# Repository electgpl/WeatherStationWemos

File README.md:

# Estación Meteorológica WiFi v1.0 

Esta es una estación Meteorológica Inalámbrica mediante WiFi, basada en el SoC ESP8266 para la comunicación y los sensores: BMP085/180, DHT11 y LDR.
Para una mejor precisión de medición, la temperatura se extrae del sensor Bosch en lugar del sensor DHT11, quedando así el DHT11 solo para indicar la humedad relativa.
El firmware cuenta con la biblioteca WiFiManager para aumentar la facilidad de autenticación para el usuario y los datos son enviados directamente a ThingSpeak.
Estos datos son enviados cada 5 minutos para mantener las buenas costumbres de frecuencia de datos en el servidor ThingSpeak, en el caso de parámetros meteorológicos no es necesaria la actualización constante de los datos, estos cambian de forma lenta.

## Controles - v1.0

  - Core - **ESP8266 - WEMOS D1 Mini**
  - Sensor de Presión y Temperatura - **BMP085 - BMP180**
  - Sensor de Humedad y Temperatura - **DHT11**
  - Sensor de Luminosidad - **LDR**
  - Botón de configuración para restablecer datos de fabrica
  - Servidor - **ThingSpeak**
  - Control WiFi - **WiFiManager**

## Alimentación

> Diseñado para ser alimentado con fuente de alimentación de 100 a 240Vac 3W

### Diseño

> Diseñado con EAGLE, en solo dos capas con componentes THT para facilitar
> la integración al alumno, el desarrollo del PCB en el hogar y mantener
> el menor costo posible.

### Medición OnLine en Tiempo Real ThingSpeak Channel 128756
https://thingspeak.com/channels/128756

Patrocinado
----
¿Dónde fabricamos nuestros PCBs?
Nuestros PCBs los fabricamos con la empresa PCBWay, esta empresa nos permite realizar pequeñas cantidades como prototipos rápidos para nuestros desarrollos a medida.
También nos permite realizar grandes producciones para realizar proyectos comerciales.
Servicio de prototipo de PCB por tan solo $5 las 10 unidades.
Cada nuevo miembro recibirá un bono de $5, más servicio express de 24Hs o 48Hs.
Servicio de ensamblado de PCB por $88 más envió gratis en todo el mundo, más esténcil, más componentes.
Un servicio de calidad!
https://www.pcbway.es/

License
----

MIT

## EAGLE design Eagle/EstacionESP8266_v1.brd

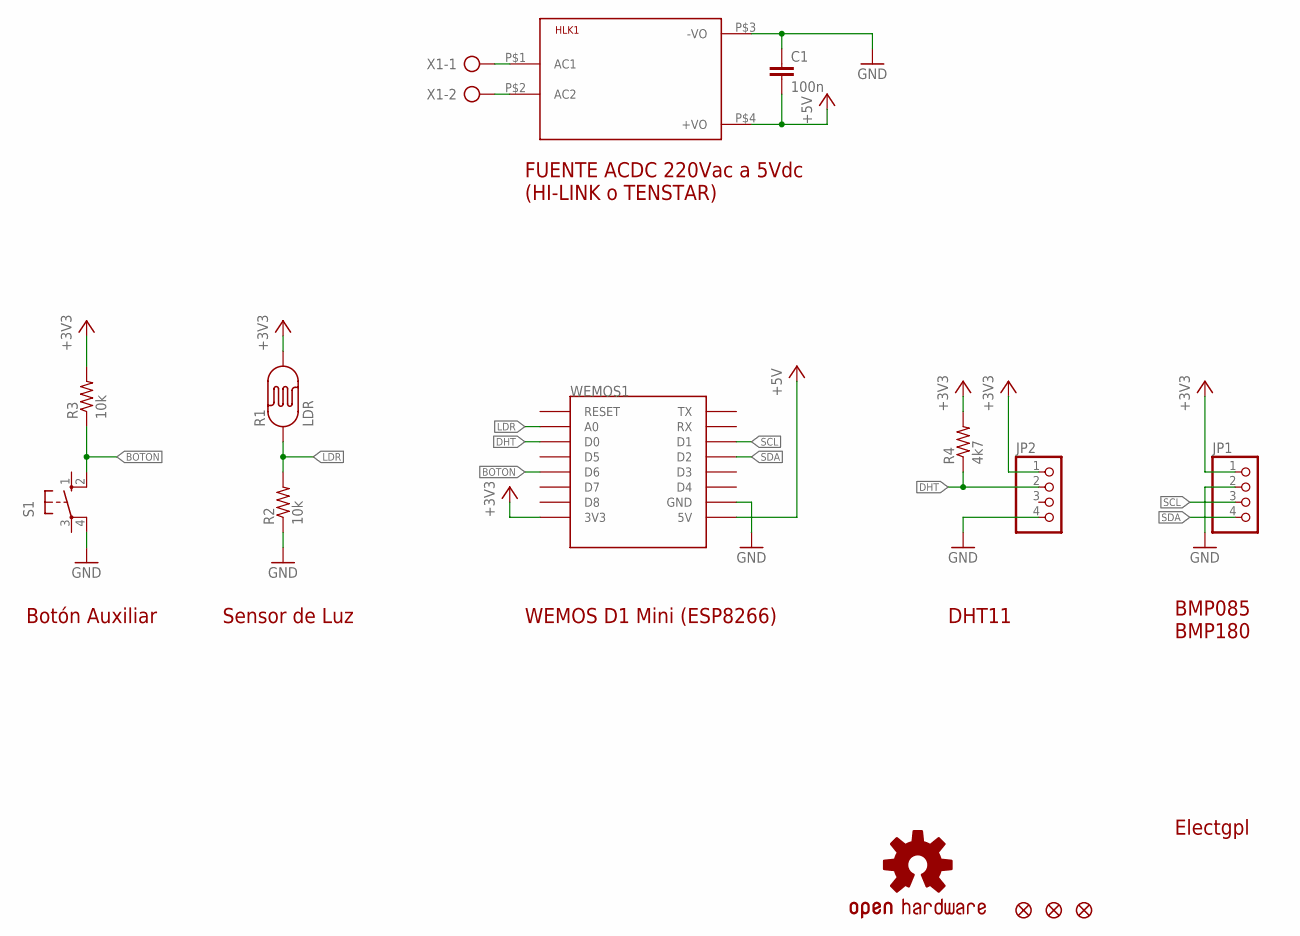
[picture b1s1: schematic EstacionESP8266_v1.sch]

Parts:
C1: 100n; C050-024X044
HLK1: HLK-PM013W; HLK-PM01
JP1, JP2: PINHD-1X4; 1X04
JP3, JP4, JP5: FIDUCIAL1.5X3; FIDUCIAL-1.5X3
R1: LDR; PHOTOCELL
R2, R3: 10k; 0204/7
R4: 4k7; 0204/7
S1: 10-XX; B3F-10XX
U$5: OSHW-LOGOM; OSHW-LOGO-M
WEMOS1: WEMOS-D1-MINI
X1: AK500/2

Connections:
+3V3: JP1.1, JP2.1, R1.2, R3.2, R4.2, WEMOS1.3V3
+5V: C1.2, HLK1.P$4 (+VO), WEMOS1.5V
BOTON: R3.1, S1.2 (S1), WEMOS1.D6
DHT: JP2.2, R4.1, WEMOS1.D0
GND: C1.1, HLK1.P$3 (-VO), JP1.2, JP2.4, R2.1, S1.4 (P1), WEMOS1.GND
LDR: R1.1, R2.2, WEMOS1.A0
unnamed: HLK1.P$1 (AC1), X1.1
unnamed: HLK1.P$2 (AC2), X1.2
SCL: JP1.3, WEMOS1.D1
SDA: JP1.4, WEMOS1.D2

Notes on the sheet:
Electgpl
BMP085 BMP180
DHT11
WEMOS D1 Mini (ESP8266)
Sensor de Luz
Botón Auxiliar
FUENTE ACDC 220Vac a 5Vdc (HI-LINK o TENSTAR)

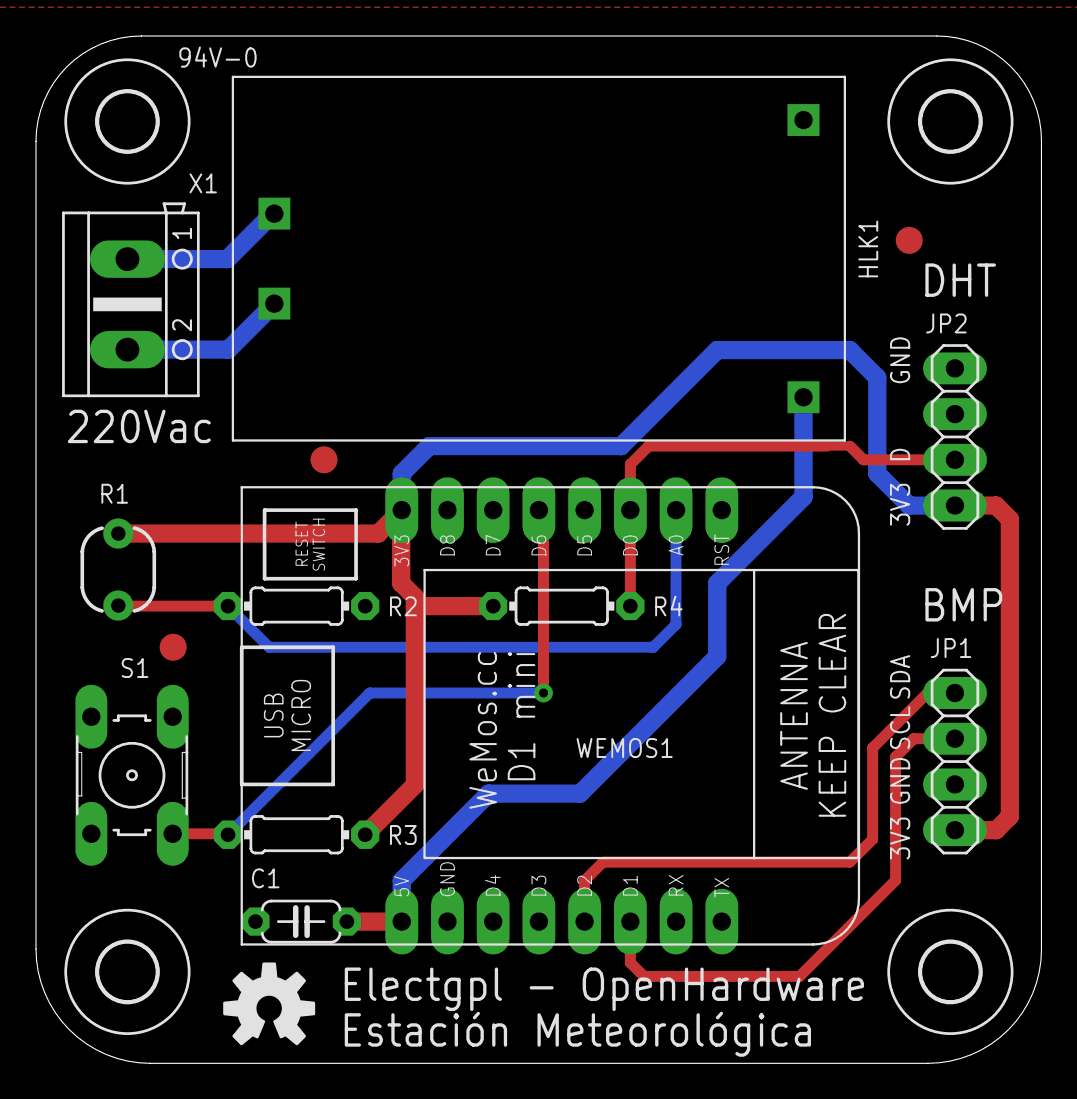
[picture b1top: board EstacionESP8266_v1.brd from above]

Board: 2 copper layers, 55.9 x 57.1 mm, 19 parts (0 on the bottom side), 10 nets.

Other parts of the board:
U$1, U$2, U$3, U$4: 3,2

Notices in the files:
parts and their libraries:
SparkFun: Licensing: CC v3.0 Share-Alike You are welcome to use this library for commercial purposes.
